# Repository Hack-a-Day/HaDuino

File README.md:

<center><H1>The HaDuino</H1>
<H3>Hackaday's own Arduino-compatible AVR development board</H3></center>
<hr>

Under our new ownership, Hackaday is now able to bring you the latest and the greatest Open Hardware projects 
designed <i>completely in house</i>. For our first such experimentation in our own custom hardware, we decided
to build what we love: an Arduino-compatable development board that blinks a LED.<p>

However, following a cursory review of existing development boards, we were somewhat dejected; we realized everything
that could be done with an Arduino board had already been done. After some serious drin^H^H^H^Hthinking, the brains
behind Hackaday came up with an entirely new paradigm for what development boards can do.<p>

<H3>It's a freakin' bottle opener<H3><p>

Really, how sweet is that? I mean just look at this thing:

Actually, it's pretty sucky as a bottle opener. We ended up breaking the first one we tested. Nevertheless, in the
spirit of open hardware, we're giving out our files and hoping some of you can improve on it. Maybe you want to
remove the pin headers and replace them with LEDs? Maybe you want to make the bottle opener actually work. That's all
fine with us. just <a href="http://hackaday.com/contact-hack-a-day/">drop us a note on our tip line</a> if you build
your own.

Oh, the back silk screen is pretty sweet:

So there you go. Schematic and BOM are in the PDF, if you get a board made (I'm sharing it 
<a href="http://oshpark.com/shared_projects/lNlBlB2y">at OSH Park</a>. It's about $30 for three boards) you most likely
already have the components to make this lying around in your parts bin. Gerbers are up as well, do with them as
you please.

Rock on.

PS: This is totally not an Arduino (Hi Massimo! Like your HaD t-shirt?) and anyone calling it that will face the fury
of a hundred goose-sized geese.

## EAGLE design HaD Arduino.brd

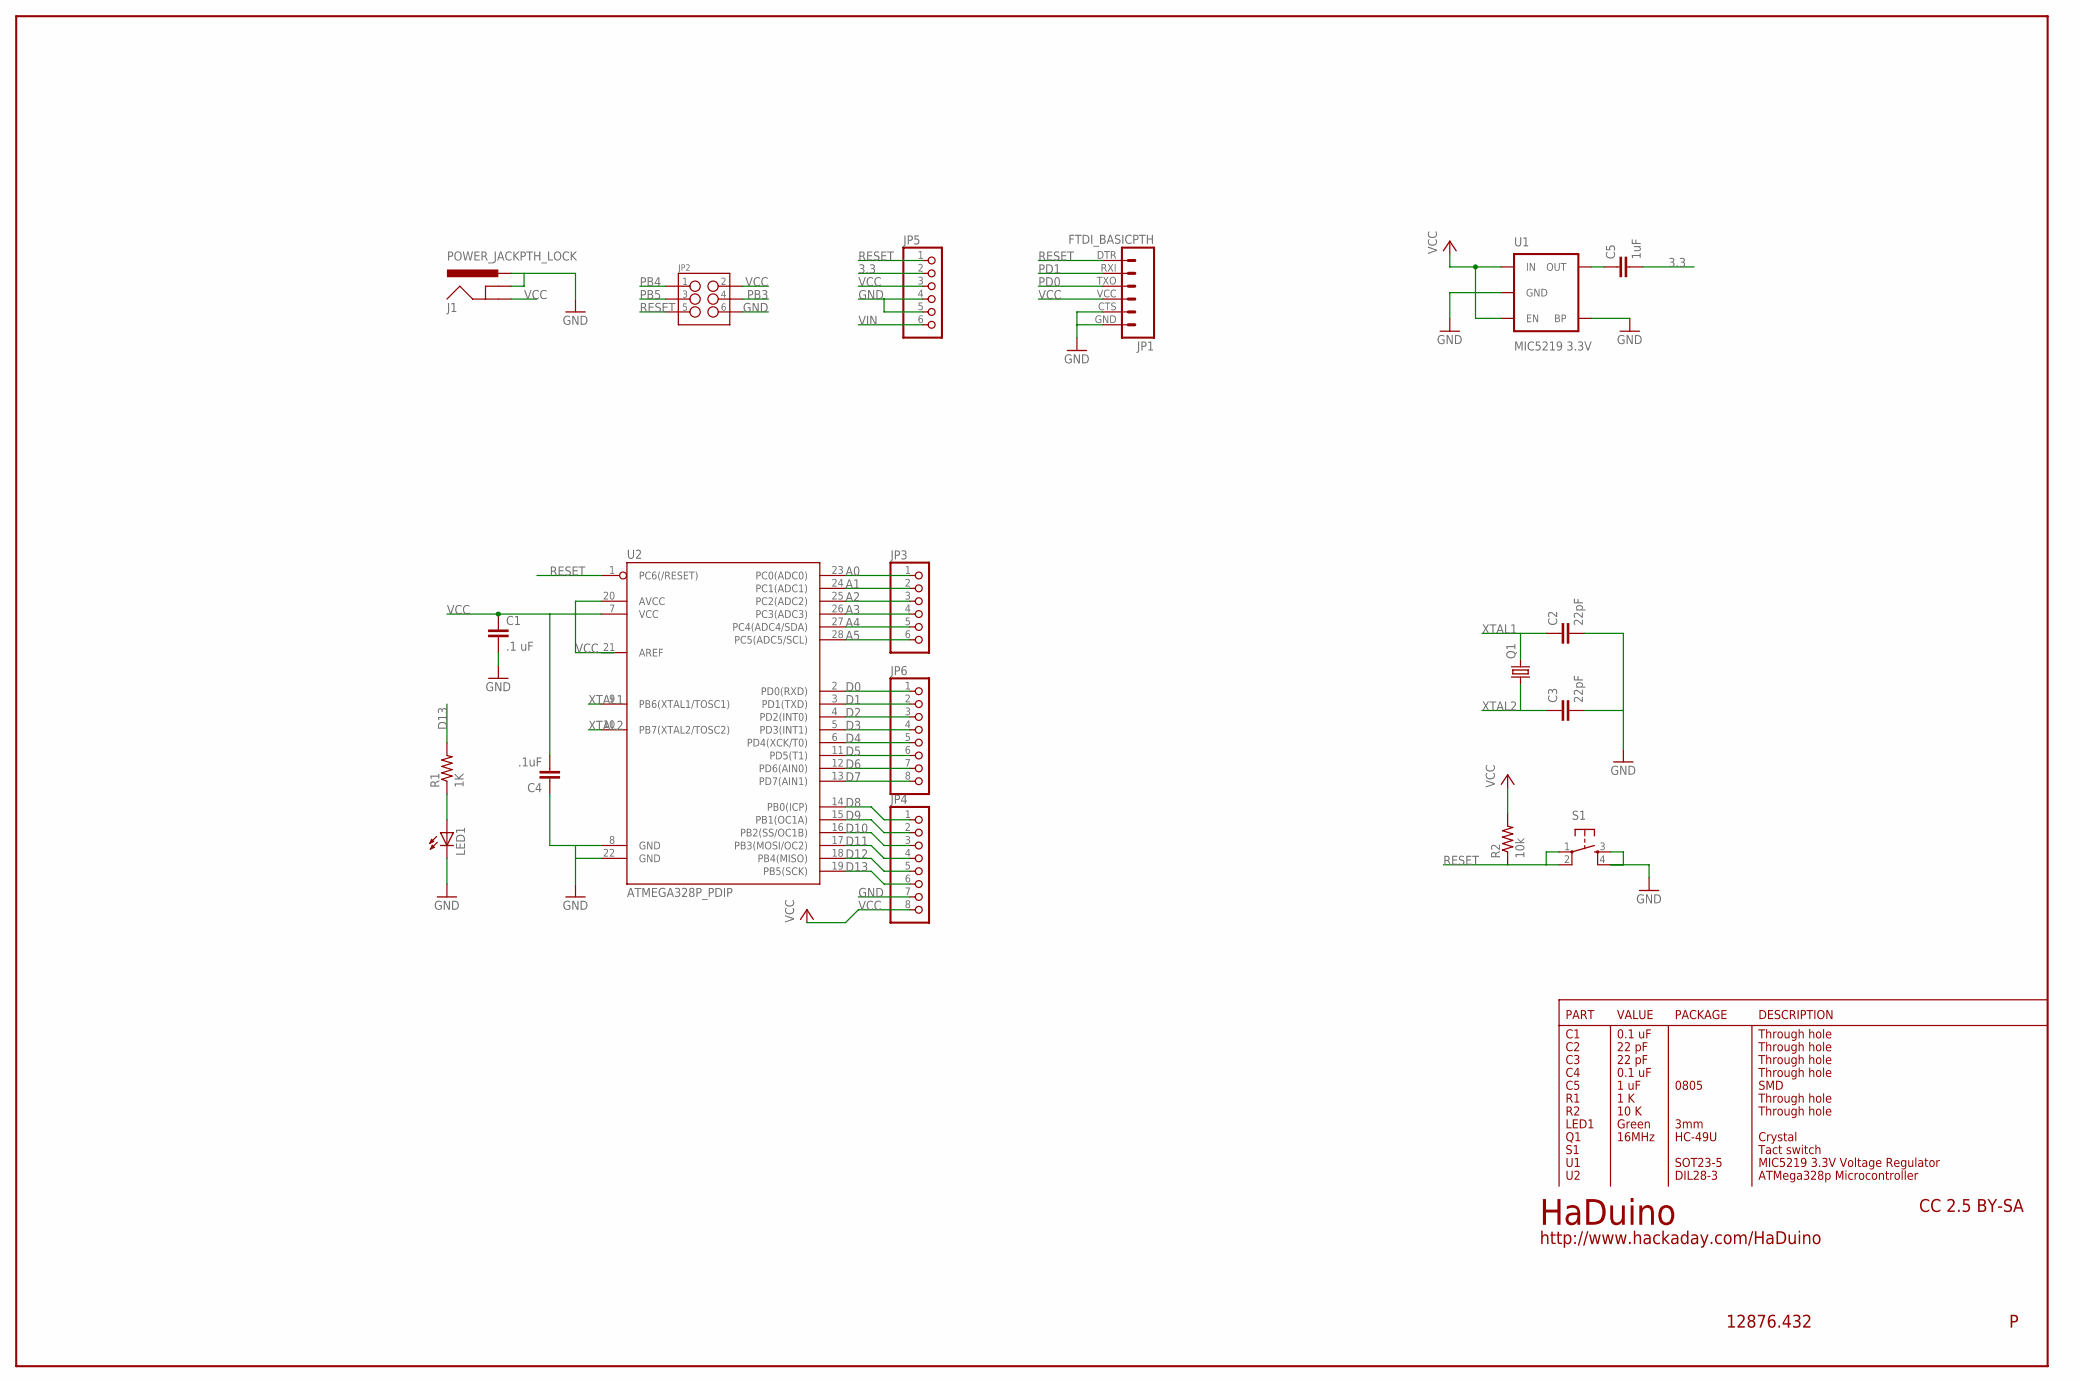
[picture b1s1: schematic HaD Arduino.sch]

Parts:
C1: .1 uF; CAP-PTH-SMALL-KIT
C2, C3: 22pF; CAP-PTH-SMALL-KIT
C4: .1uF; CAP-PTH-SMALL-KIT
C5: 1uF; 0805
J1: POWER_JACKPTH_LOCK; POWER_JACK_PTH_LOCK
JP1: FTDI_BASICPTH; FTDI_BASIC
JP2: M03X2POGO_PINS; 2X3_POGO
JP3, JP5: PINHD-1X6B; 1X06-BIG
JP4, JP6: PINHD-1X8BIG; 1X08-BIG
LED1: LED3MM
Q1: CRYTALHC49U-V; HC49U-V
R1: 1K; AXIAL-0.3-KIT
R2: 10k; AXIAL-0.3-KIT
S1: TAC_SWITCHPTH; TACTILE-PTH
U1: MIC5219 3.3V; SOT23-5
U2: ATMEGA328P_PDIP; DIL28-3

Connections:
3.3: C5.2, JP5.2
A0: JP3.1, U2.23 (PC0(ADC0))
A1: JP3.2, U2.24 (PC1(ADC1))
A2: JP3.3, U2.25 (PC2(ADC2))
A3: JP3.4, U2.26 (PC3(ADC3))
A4: JP3.5, U2.27 (PC4(ADC4/SDA))
A5: JP3.6, U2.28 (PC5(ADC5/SCL))
D0: JP6.1, U2.2 (PD0(RXD))
D1: JP6.2, U2.3 (PD1(TXD))
D2: JP6.3, U2.4 (PD2(INT0))
D3: JP6.4, U2.5 (PD3(INT1))
D4: JP6.5, U2.6 (PD4(XCK/T0))
D5: JP6.6, U2.11 (PD5(T1))
D6: JP6.7, U2.12 (PD6(AIN0))
D7: JP6.8, U2.13 (PD7(AIN1))
D8: JP4.1, U2.14 (PB0(ICP))
D9: JP4.2, U2.15 (PB1(OC1A))
D10: JP4.3, U2.16 (PB2(SS/OC1B))
D11: JP4.4, U2.17 (PB3(MOSI/OC2))
D12: JP4.5, U2.18 (PB4(MISO))
D13: JP4.6, R1.P$2 (2), U2.19 (PB5(SCK))
GND: C1.2, C2.2, C3.2, C4.1, J1.GNDBREAK, J1.PWR, JP1.CTS (5), JP1.GND (6), JP2.P$6 (6), JP4.7, JP5.4, JP5.5, LED1.K (C), S1.3, S1.4, U1.2 (GND), U1.4 (BP), U2.8 (GND), U2.22 (GND)
unnamed: LED1.A, R1.P$1 (1)
unnamed: C5.1, U1.5 (OUT)
PB3: JP2.P$4 (4)
PB4: JP2.P$1 (1)
PB5: JP2.P$3 (3)
PD0: JP1.TXO (3)
PD1: JP1.RXI (2)
RESET: JP1.DTR (1), JP2.P$5 (5), JP5.1, R2.P$1 (1), S1.1, S1.2, U2.1 (PC6(/RESET))
VCC: C1.1, C4.2, J1.GND, JP1.VCC (4), JP2.P$2 (2), JP4.8, JP5.3, R2.P$2 (2), U1.1 (IN), U1.3 (EN), U2.7 (VCC), U2.20 (AVCC), U2.21 (AREF)
VIN: JP5.6
XTAL1: C2.1, Q1.2, U2.9 (PB6(XTAL1/TOSC1))
XTAL2: C3.1, Q1.1, U2.10 (PB7(XTAL2/TOSC2))

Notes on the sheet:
VALUE
PART
PACKAGE
DESCRIPTION
LED1
Green
3mm
16MHz
HC-49U
Through hole
0.1 uF
22 pF
1 uF
0805
SMD
1 K
10 K
Crystal
Tact switch
SOT23-5
MIC5219 3.3V Voltage Regulator
ATMega328p Microcontroller
DIL28-3
CC 2.5 BY-SA
HaDuino
http://www.hackaday.com/HaDuino
12876.432

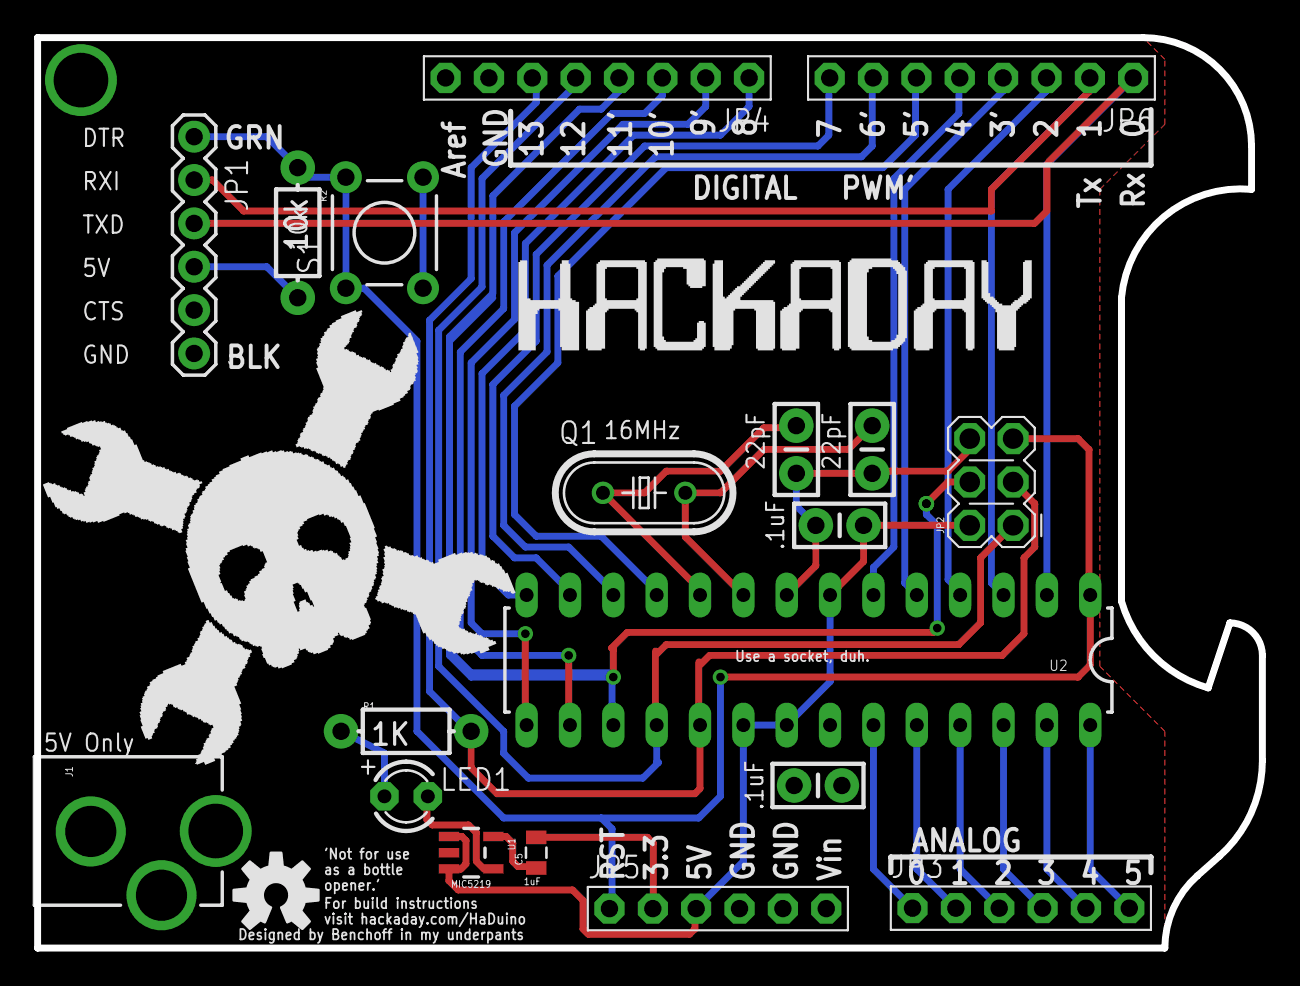
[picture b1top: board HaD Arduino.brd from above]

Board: 2 copper layers, 71.8 x 53.3 mm, 20 parts (0 on the bottom side), 28 nets.

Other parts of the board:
U$1: OSHW-LOGO-M

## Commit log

2013-10-10 First, and probably last commit
2013-10-10 damnit

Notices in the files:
parts and their libraries:
SparkFun-DigitalIC: Licensing: CC v3.0 Share-Alike You are welcome to use this library for commercial purposes.
